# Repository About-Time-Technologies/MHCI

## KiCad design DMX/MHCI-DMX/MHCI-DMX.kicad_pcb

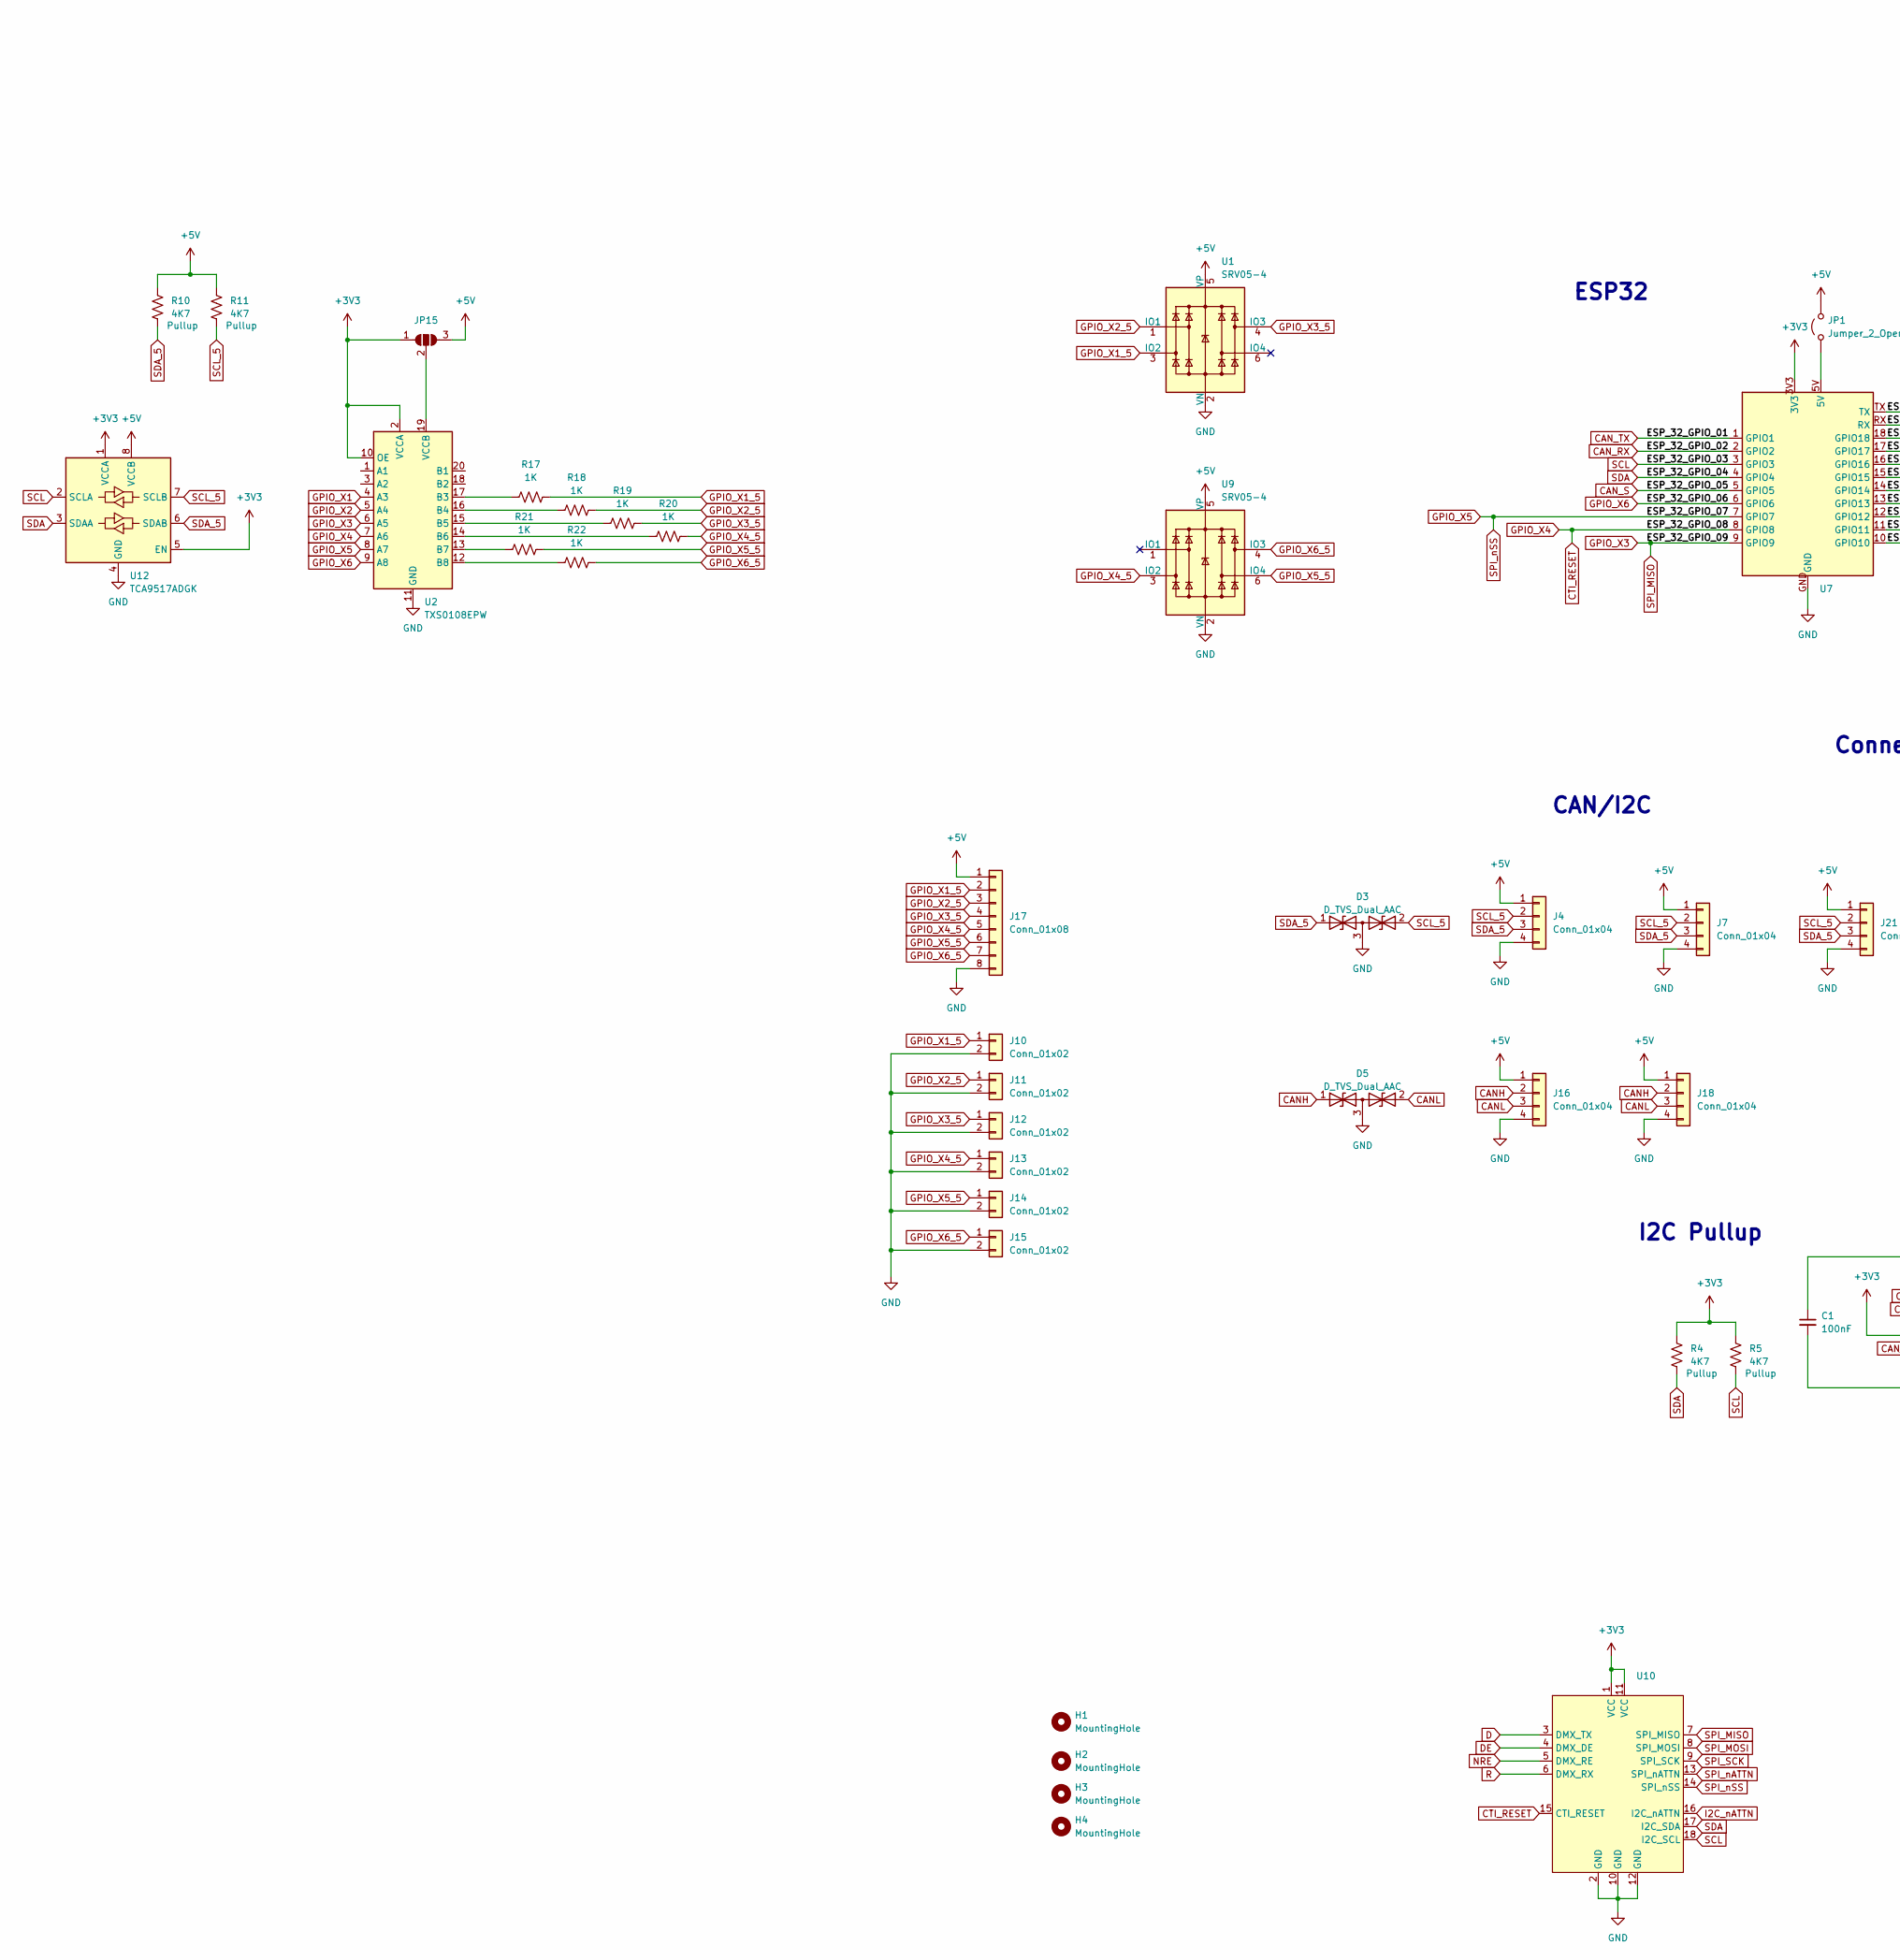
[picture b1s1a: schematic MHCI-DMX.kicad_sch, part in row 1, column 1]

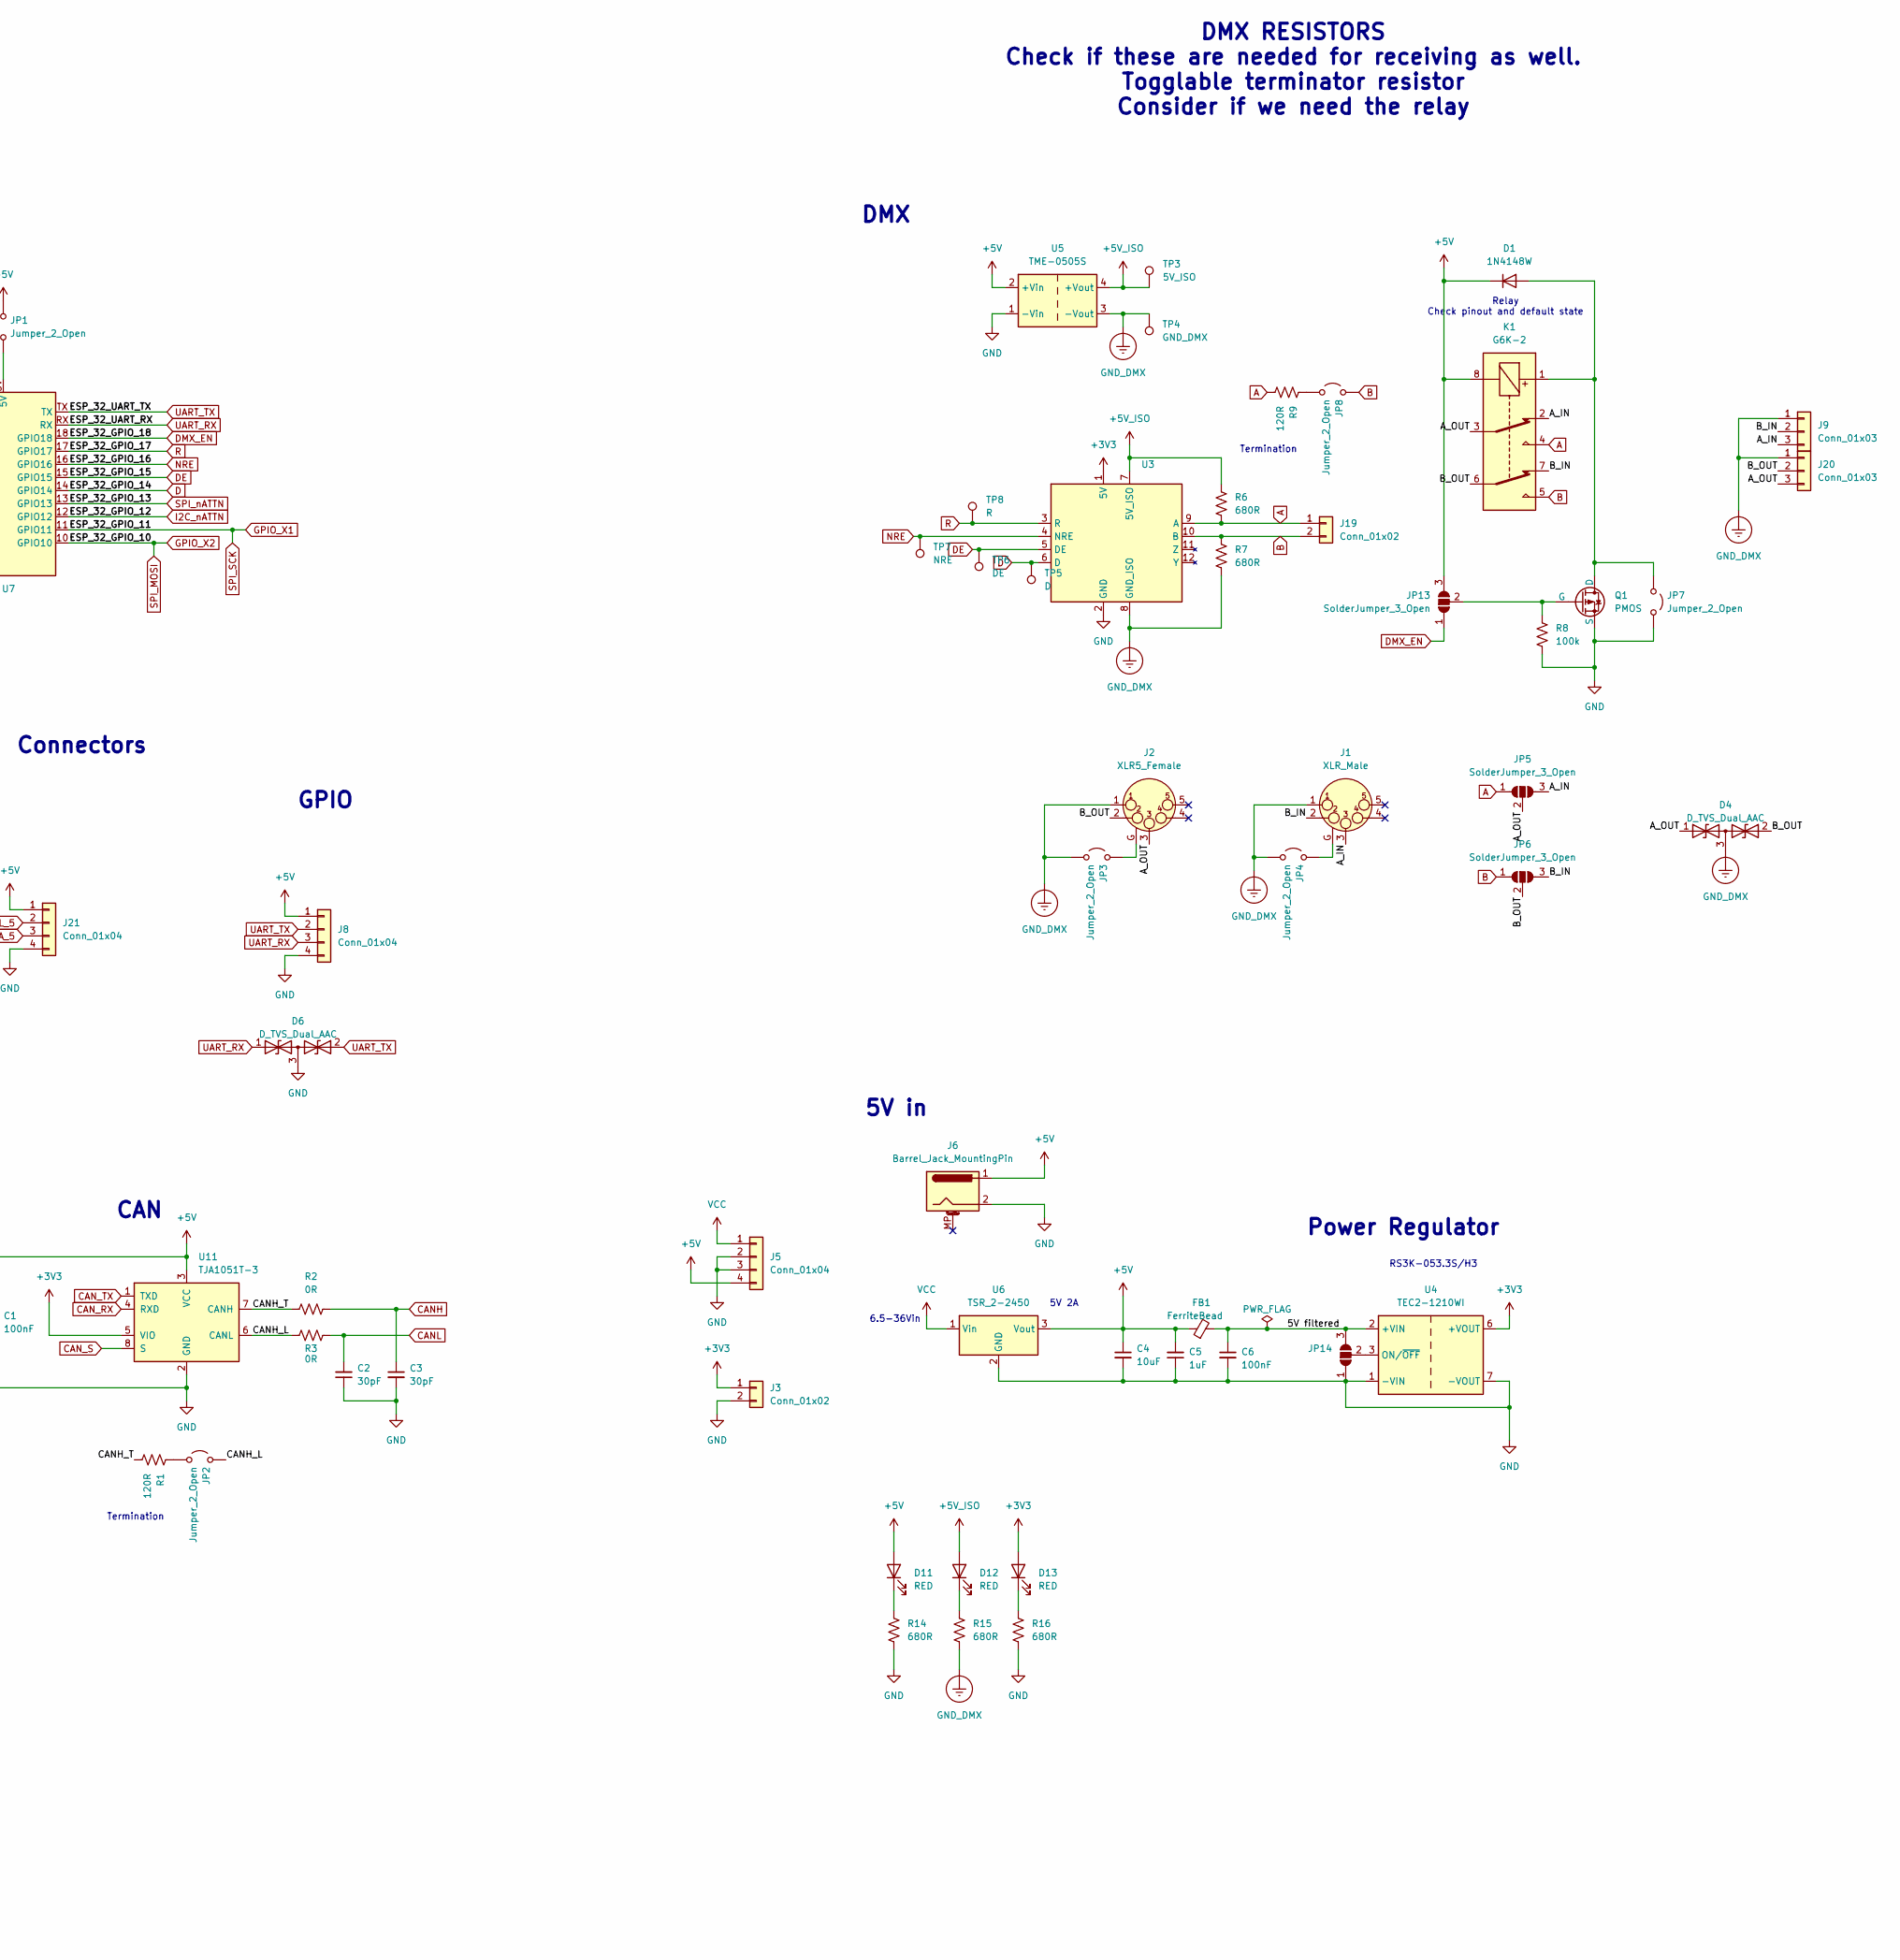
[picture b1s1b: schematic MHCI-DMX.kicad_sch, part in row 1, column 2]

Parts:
C1, C6: 100nF; C_0402_1005Metric; LCSC C1525
C2, C3: 30pF; C_0402_1005Metric; LCSC C1570
C4: 10uF; C_0603_1608Metric; LCSC C96446
C5: 1uF; C_0402_1005Metric; LCSC C52923
D1: 1N4148W; D_SOD-123; LCSC C2099
D3, D4, D5, D6: D_TVS_Dual_AAC; SOT-23; LCSC C32677
D11, D12, D13: RED; LED_0603_1608Metric; LCSC C2286
FB1: FerriteBead; D_0805_2012Metric; LCSC C1015
H1, H2, H3, H4: MountingHole; MountingHole_3.2mm_M3
J1: XLR_Male; Jack_XLR_Neutrik_NC5MAH_LR
J2: XLR5_Female; Jack_XLR_Neutrik_NC5FAH_LR-DAE
J3, J19: Conn_01x02; PinHeader_1x02_P2.54mm_Vertical
J4, J7, J8, J16, J18: Conn_01x04; PinSocket_1x04_P2.54mm_Vertical
J5: Conn_01x04; PinHeader_1x04_P2.54mm_Vertical
J6: Barrel_Jack_MountingPin; BarrelJack_GCT_DCJ200-10-A_Horizontal
J9, J20: Conn_01x03; JST_XH_B3B-XH-AM_1x03_P2.50mm_Vertical
J10, J11, J12, J13, J14, J15: Conn_01x02; 2060-452-998-404 Wago
J17: Conn_01x08; PinSocket_1x08_P2.54mm_Vertical
J21: Conn_01x04; JST_XH_B4B-XH-AM_1x04_P2.50mm_Vertical
JP1, JP2, JP3, JP4, JP7, JP8: Jumper_2_Open; SolderJumper-2_P1.3mm_Open_RoundedPad1.0x1.5mm
JP5, JP6, JP13, JP14, JP15: SolderJumper_3_Open; SolderJumper-3_P1.3mm_Open_RoundedPad1.0x1.5mm
K1: G6K-2; Relay_DPDT_Omron_G6K-2F
Q1: PMOS; SOT-23; LCSC C10487
R1, R9: 120R; R_0402_1005Metric; LCSC C25079
R2, R3: 0R; R_0402_1005Metric; LCSC C17168
R4, R5, R10, R11: 4K7; R_0603_1608Metric; LCSC C23162
R6, R7: 680R; R_0402_1005Metric; LCSC C25130
R8: 100k; R_0603_1608Metric; LCSC C25803
R14, R15, R16: 680R; R_0603_1608Metric; LCSC C23228
R17, R18, R19, R20, R21, R22: 1K; R_0603_1608Metric; LCSC C21190
TP3: 5V_ISO; TestPoint_Pad_D1.0mm
TP4: GND_DMX; TestPoint_Pad_D1.0mm
TP5: D; TestPoint_Pad_D1.0mm
TP6: DE; TestPoint_Pad_D1.0mm
TP7: NRE; TestPoint_Pad_D1.0mm
TP8: R; TestPoint_Pad_D1.0mm
U1, U9: SRV05-4; SOT-23-6; LCSC C85364
U2: TXS0108EPW; TSSOP-20_4.4x6.5mm_P0.65mm; LCSC C17206
U3: ISO-DMX
U4: TEC2-1210WI; Converter_DCDC_TRACO_TMR-xxxx_THT
U5: TME-0505S; Converter_DCDC_TRACO_TME_03xxS_05xxS_12xxS_Single_THT
U6: TSR_2-2450; Converter_DCDC_TRACO_TSR-1_THT
U7: ESP-32-S3-Tiny - PTH
U10: WirelessDMX-Module
U11: TJA1051T-3; SOIC-8_3.9x4.9mm_P1.27mm; LCSC C5342108
U12: TCA9517ADGK; VSSOP-8_3x3mm_P0.65mm; LCSC C201698

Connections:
+3V3: D13.2 (A), J3.1, JP15.1 (A), R4.1, R5.1, U2.2 (VCCA), U2.10 (OE), U3.1 (5V), U4.6 (+VOUT), U7.3V3, U10.1 (VCC), U10.11 (VCC), U11.5 (VIO), U12.1 (VCCA), U12.5 (EN)
+5V: C1.1, C4.1, C5.2, D1.1 (K), D11.2 (A), FB1.1, J4.1, J5.4, J6.1, J7.1, J8.1, J16.1, J17.1, J18.1, J21.1, JP1.2 (B), JP13.3 (B), JP15.3 (B), K1.8, R10.1, R11.1, U1.5 (VP), U5.2 (+Vin), U6.3 (Vout), U9.5 (VP), U11.3 (VCC), U12.8 (VCCB)
+5V_ISO: D12.2 (A), R6.2, TP3.1, U3.7 (5V_ISO), U5.4 (+Vout)
/5V filtered: C6.1, FB1.2, JP14.3 (B), U4.2 (+VIN)
/A_IN: J1.3, J9.3, JP5.3 (B), K1.2
/A_OUT: D4.1 (A1), J2.3, J20.3, JP5.2 (C), K1.3
/B_IN: J1.2, J9.2, JP6.3 (B), K1.7
/B_OUT: D4.2 (A2), J2.2, J20.2, JP6.2 (C), K1.6
/CANH_L: JP2.2 (B), R3.1, U11.6 (CANL)
/CANH_T: R1.1, R2.2, U11.7 (CANH)
A: J19.1, JP5.1 (A), K1.4, R6.1, R9.1, U3.9 (A)
B: J19.2, JP6.1 (A), JP8.2 (B), K1.5, R7.2, U3.10 (B)
CANH: C3.1, D5.1 (A1), J16.2, J18.2, R2.1
CANL: C2.2, D5.2 (A2), J16.3, J18.3, R3.2
CAN_RX: U7.2 (GPIO2), U11.4 (RXD)
CAN_S: U7.5 (GPIO5), U11.8 (S)
CAN_TX: U7.1 (GPIO1), U11.1 (TXD)
CTI_RESET: U2.7 (A6), U7.8 (GPIO8), U10.15 (CTI_RESET)
D: TP5.1, U3.6 (D), U7.14 (GPIO14), U10.3 (DMX_TX)
DE: TP6.1, U3.5 (DE), U7.15 (GPIO15), U10.4 (DMX_DE)
DMX_EN: JP13.1 (A), U7.18 (GPIO18)
GND: C1.2, C2.1, C3.2, C4.2, C5.1, C6.2, D3.3 (common), D5.3 (common), D6.3 (common), J3.2, J4.4, J5.2, J5.3, J6.2, J7.4, J8.4, J10.2, J11.2, J12.2, J13.2, J14.2, J15.2, J16.4, J17.8, J18.4, J21.4, JP7.2 (B), JP14.1 (A), Q1.2 (S), R8.2, R14.2, R16.2, U1.2 (VN), U2.11 (GND), U3.2 (GND), U4.1 (-VIN), U4.7 (-VOUT), U5.1 (-Vin), U6.2 (GND), U7.GND, U9.2 (VN), U10.2 (GND), U10.10 (GND), U10.12 (GND), U11.2 (GND), U12.4 (GND)
GND_DMX: D4.3 (common), J1.1, J2.1, J9.1, J20.1, JP3.1 (A), JP4.1 (A), R7.1, R15.2, TP4.1, U3.8 (GND_ISO), U5.3 (-Vout)
GPIO_X1: U2.4 (A3), U7.11 (GPIO11), U10.9 (SPI_SCK)
GPIO_X1_5: J10.1, J17.2, R17.2, U1.3 (IO2)
GPIO_X2: U2.5 (A4), U7.10 (GPIO10), U10.8 (SPI_MOSI)
GPIO_X2_5: J11.1, J17.3, R18.2, U1.1 (IO1)
GPIO_X3: U2.6 (A5), U7.9 (GPIO9), U10.7 (SPI_MISO)
GPIO_X3_5: J12.1, J17.4, R19.2, U1.4 (IO3)
GPIO_X4_5: J13.1, J17.5, R20.2, U9.3 (IO2)
GPIO_X5: U2.8 (A7), U7.7 (GPIO7), U10.14 (SPI_nSS)
GPIO_X5_5: J14.1, J17.6, R21.2, U9.6 (IO4)
GPIO_X6: U2.9 (A8), U7.6 (GPIO6)
GPIO_X6_5: J15.1, J17.7, R22.2, U9.4 (IO3)
I2C_nATTN: U7.12 (GPIO12), U10.16 (I2C_nATTN)
NRE: TP7.1, U3.4 (NRE), U7.16 (GPIO16), U10.5 (DMX_RE)
unnamed: D1.2 (A), JP7.1 (A), K1.1, Q1.3 (D)
unnamed: D11.1 (K), R14.1
unnamed: D12.1 (K), R15.1
unnamed: D13.1 (K), R16.1
unnamed: JP1.1 (A), U7.5V
unnamed: JP2.1 (A), R1.2
unnamed: J2.G, JP3.2 (B)
unnamed: J1.G, JP4.2 (B)
unnamed: JP8.1 (A), R9.2
unnamed: JP13.2 (C), Q1.1 (G), R8.1
unnamed: JP14.2 (C), U4.3 (ON/~OFF)
unnamed: JP15.2 (C), U2.19 (VCCB)
unnamed: R17.1, U2.17 (B3)
unnamed: R18.1, U2.16 (B4)
unnamed: R19.1, U2.15 (B5)
unnamed: R20.1, U2.14 (B6)
unnamed: R21.1, U2.13 (B7)
unnamed: R22.1, U2.12 (B8)
R: TP8.1, U3.3 (R), U7.17 (GPIO17), U10.6 (DMX_RX)
SCL: R5.2, U7.3 (GPIO3), U10.18 (I2C_SCL), U12.2 (SCLA)
SCL_5: D3.2 (A2), J4.2, J7.2, J21.2, R11.2, U12.7 (SCLB)
SDA: R4.2, U7.4 (GPIO4), U10.17 (I2C_SDA), U12.3 (SDAA)
SDA_5: D3.1 (A1), J4.3, J7.3, J21.3, R10.2, U12.6 (SDAB)
SPI_nATTN: U7.13 (GPIO13), U10.13 (SPI_nATTN)
UART_RX: D6.1 (A1), J8.3, U7.RX
UART_TX: D6.2 (A2), J8.2, U7.TX
VCC: J5.1, U6.1 (Vin)

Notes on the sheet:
Connectors
5V 2A
CAN
DMX
Termination
RS3K-053.3S/H3
5V in
Relay Check pinout and default state
ESP32
CAN/I2C
I2C Pullup
DMX RESISTORS Check if these are needed for receiving as well. Togglable terminator resistor Consider if we need the relay
GPIO
Power Regulator
6.5-36Vin

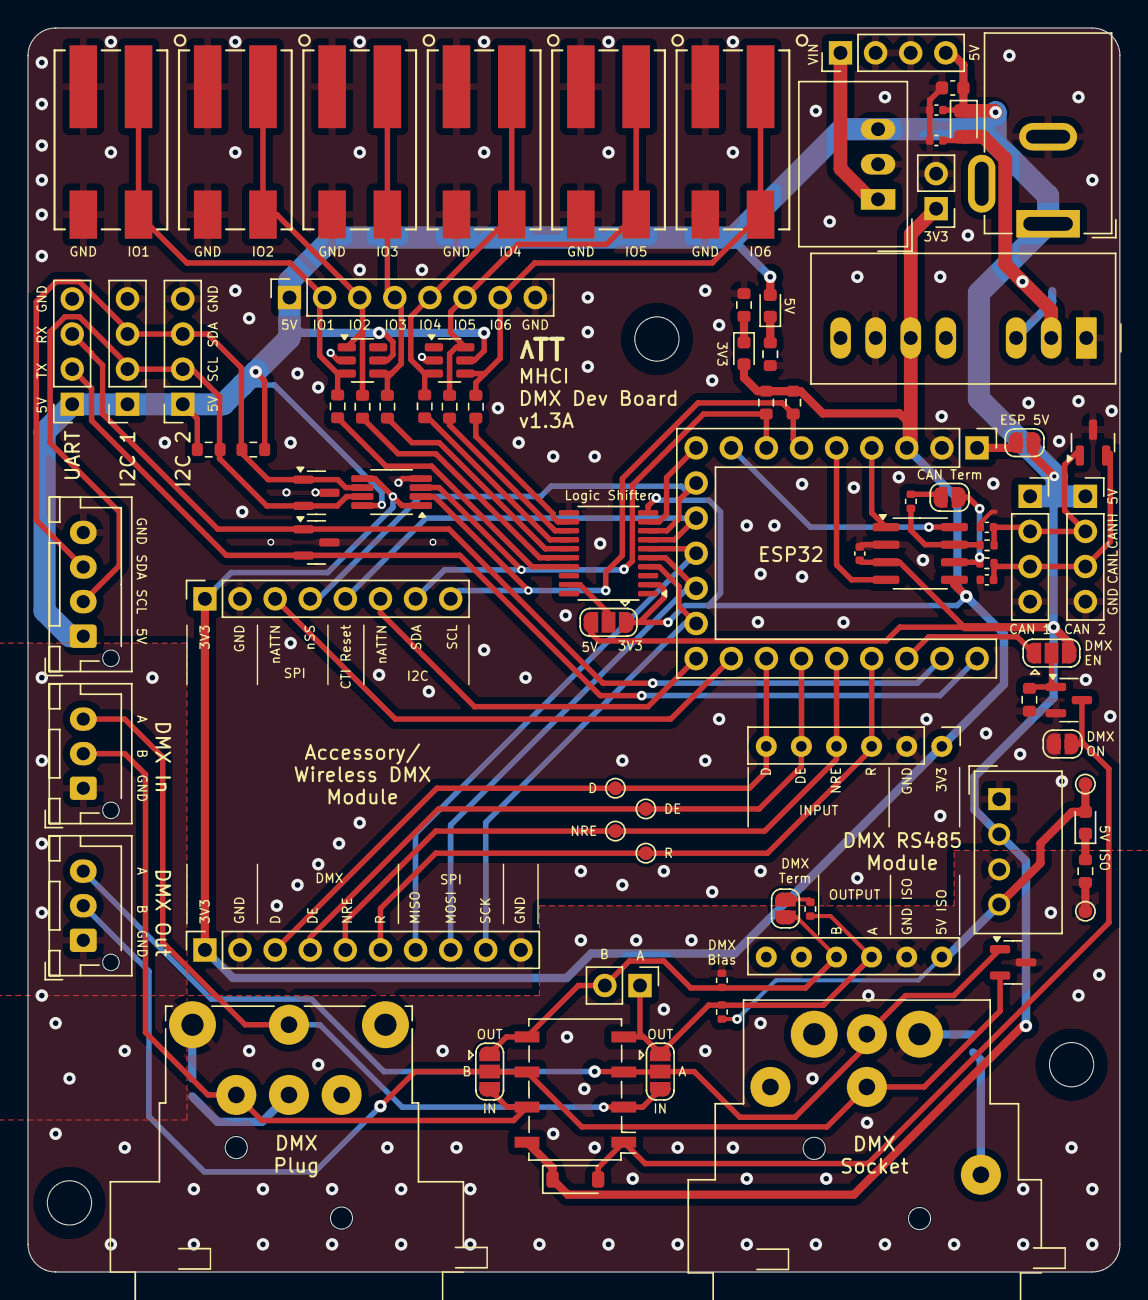
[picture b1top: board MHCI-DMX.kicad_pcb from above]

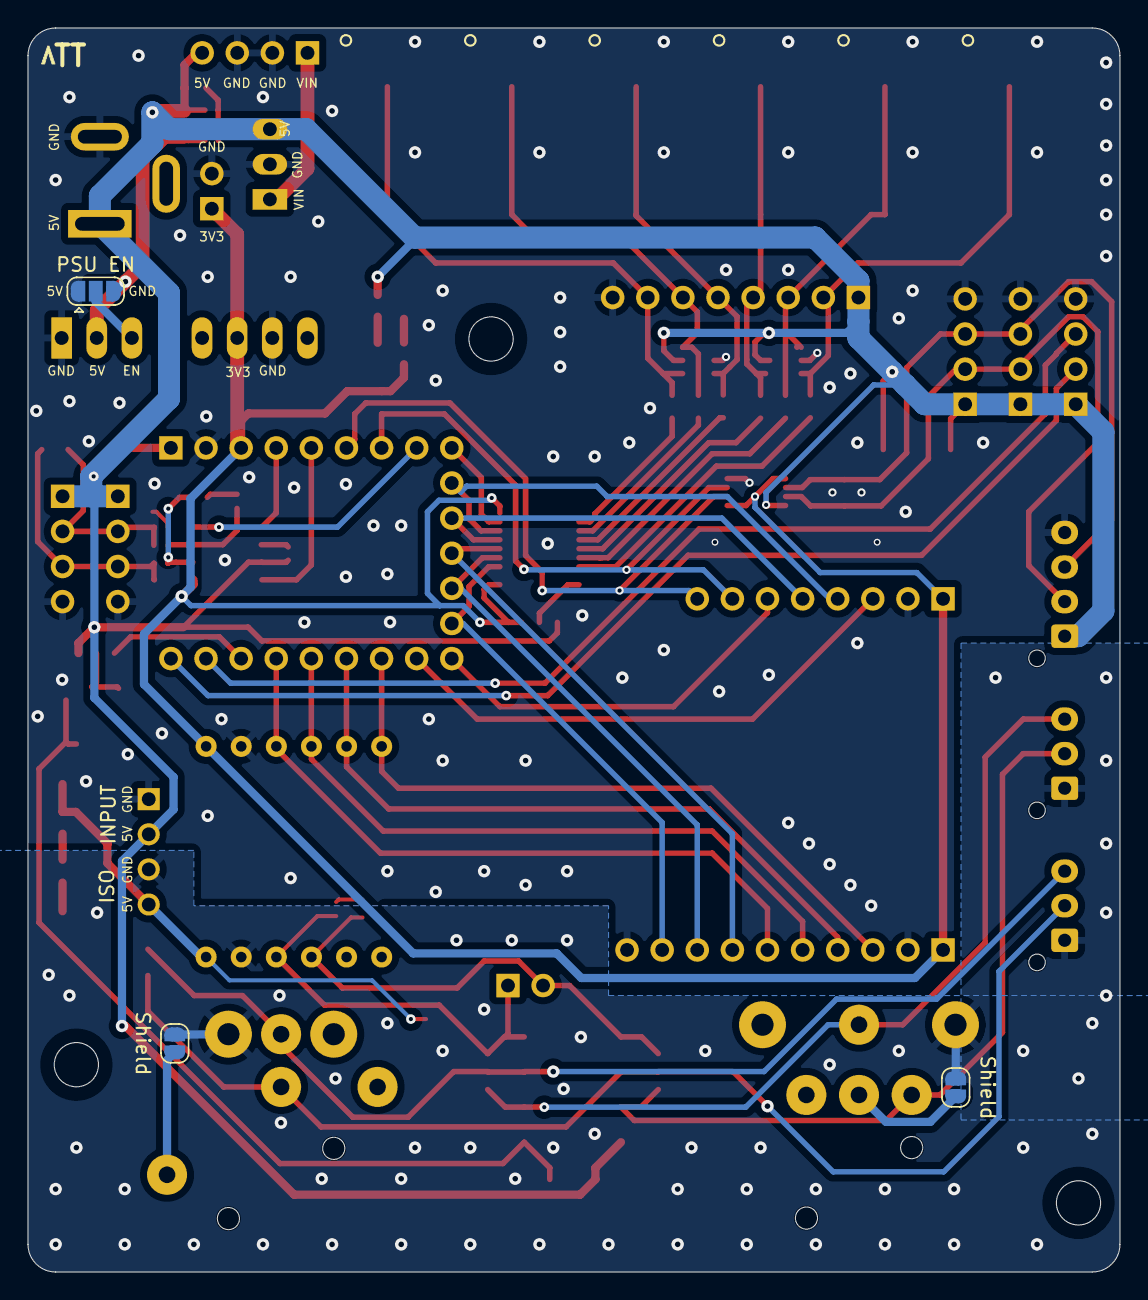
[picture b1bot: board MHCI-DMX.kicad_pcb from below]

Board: 2 copper layers, 79.0 x 90.0 mm, 89 parts (3 on the bottom side), 63 nets.

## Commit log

2025-07-24 Adding 680R bias resistor network
2025-08-18 Functional hazer control
2025-08-21 New screen
2025-09-03 Functional display
2025-09-03 Virtual button state machine
2025-09-03 Functional double click
2025-09-03 Complete tidy up
2025-09-04 Encoder transition
2025-09-04 Functional callback passthrough
2025-09-04 Back to where we were...
2025-09-04 State saving
2025-09-04 Neopixel control
2025-09-04 Prototype LED control
2025-09-04 Fix PWM GPIO values
2025-09-04 Add "find hazer"
2025-09-04 Fix casting of address to uint8_t
2025-09-04 Split out control and ui state
2025-09-04 Split out neopixel update and show
2025-09-04 Adjusting UI alignment and LED label
2025-10-09 Change hazeOn to only be true when level is > 0
2025-10-10 Matching Eos profile for haze and unit on values
2025-11-05 Functional - needs stripping back
2025-11-05 Slimline control functionality
2025-11-06 Add multiple alert options to the display

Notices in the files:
parts and their libraries:
Copyright 2016 Accelerated Designs. All rights reserved.
